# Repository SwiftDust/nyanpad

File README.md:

# Nyanpad

My macropad, built for [Hackpad](https://hackpad.hackclub.com)! It features LED backlighting, an OLED screen and 4 keys to control your music :)

## CAD
https://cad.onshape.com/documents/298fb66352279c3f6c87f3de/w/c801169e636e5dfcfdb9d4bb/e/7bab212490aaadabd4187f28?renderMode=0&uiState=6afa35f24b47de4cd4f44e78

## Schematic

## PCB

## BOM

| Qty | Item | Price (USD) | Link |
|---|---|---|---|
| 4x | Cherry MX Switches | 5,29 | https://nl.aliexpress.com/item/1005012832907656.html?spm=a2g0o.productlist.main.16.54f74710lBx9J8&algo_pvid=466906ea-7de0-4691-b869-b8c9dada8754&algo_exp_id=466906ea-7de0-4691-b869-b8c9dada8754-15&pdp_ext_f={%22order%22%3A%2254%22%2C%22eval%22%3A%221%22%2C%22fromPage%22%3A%22search%22}&pdp_npi=6%40dis!EUR!5.37!4.79!!!5.80!5.18!%400b88a95617947775685107257e0f20!12000059458181010!sea!NL!0!X!1!0!n_tag%3A-29919%3Bd%3Aeac98f9%3Bm03_new_user%3A-29895%3BpisId%3A5000000220770329&curPageLogUid=bMwGbcEopLZR&utparam-url=scene%3Asearch|query_from%3A|x_object_id%3A1005012832907656|_p_origin_prod%3A |
| 4x | DSA keycaps | 1,59 | https://nl.aliexpress.com/item/1005013428750906.html?spm=a2g0o.productlist.main.13.7f60bf6anoDfJp&algo_pvid=8e305201-02fd-4fef-ae02-85556622e4f5&algo_exp_id=8e305201-02fd-4fef-ae02-85556622e4f5-12&pdp_ext_f={%22order%22%3A%2210%22%2C%22eval%22%3A%221%22%2C%22fromPage%22%3A%22search%22}&pdp_npi=6%40dis!EUR!0.35!0.36!!!2.49!2.58!%400b15832917947779250776391e0fc9!12000061069461267!sea!NL!0!X!1!0!n_tag%3A-29919%3Bd%3Aeac98f9%3Bm03_new_user%3A-29895&curPageLogUid=Cd40D66sFnz9&utparam-url=scene%3Asearch|query_from%3A|x_object_id%3A1005013428750906|_p_origin_prod%3A |
| 5x | M3x5x4 heatset inserts | 4,51 | https://nl.aliexpress.com/item/1005010155305523.html?spm=a2g0o.productlist.main.1.5f0a3c4fNBxcuN&algo_pvid=e5bb6dcb-2cde-4527-a1a4-0230e28a1f05&algo_exp_id=e5bb6dcb-2cde-4527-a1a4-0230e28a1f05-0&pdp_ext_f={%22order%22%3A%2210565%22%2C%22eval%22%3A%221%22%2C%22orig_sl_item_id%22%3A%221005010155305523%22%2C%22orig_item_id%22%3A%221005013150425438%22%2C%22fromPage%22%3A%22search%22}&pdp_npi=6%40dis!EUR!8.18!4.09!!!58.89!29.44!%400b88ab8a17947781676843401e0e3c!12000051347301636!sea!NL!0!X!1!0!n_tag%3A-29919%3Bd%3Aeac98f9%3Bm03_new_user%3A-29895&curPageLogUid=PFmU9B7g3e2J&utparam-url=scene%3Asearch|query_from%3A|x_object_id%3A1005010155305523|_p_origin_prod%3A1005013150425438 |
| 6x | 1N4148 DO-35 diodes | 0,47 | https://www.lcsc.com/product-detail/C402212.html?s_z=n_q_t_1N4148 |
| 4x | SK6812 MINI-E LEDs  | 0,41 | https://www.lcsc.com/product-detail/C5149201.html?s_z=s_q_SK6812MINI-E |
| 1x | 0,91" 128x32 OLED display | 2,27 | https://www.lcsc.com/product-detail/C5248081.html?s_z=s_c_LCD%252C%2520OLED%252C%2520Graphic |
| 1x | XIAO RP2040 | 3,90 | https://www.seeedstudio.com/XIAO-RP2040-v1-0-p-5026.html |
| 1x | PCB | 4,00 | https://jlcpcb.com/ |
| | Total | 22,44 | |
| | Total with shipping* | 49,73

*Shipping: 2,79 for shipping JLCPCB to LCSC, 13,90 to ship that order to me, 8,16 for the SEED XIAO RP2040 and 2,44 for the Aliexpress order. Printing Legion not yet included.

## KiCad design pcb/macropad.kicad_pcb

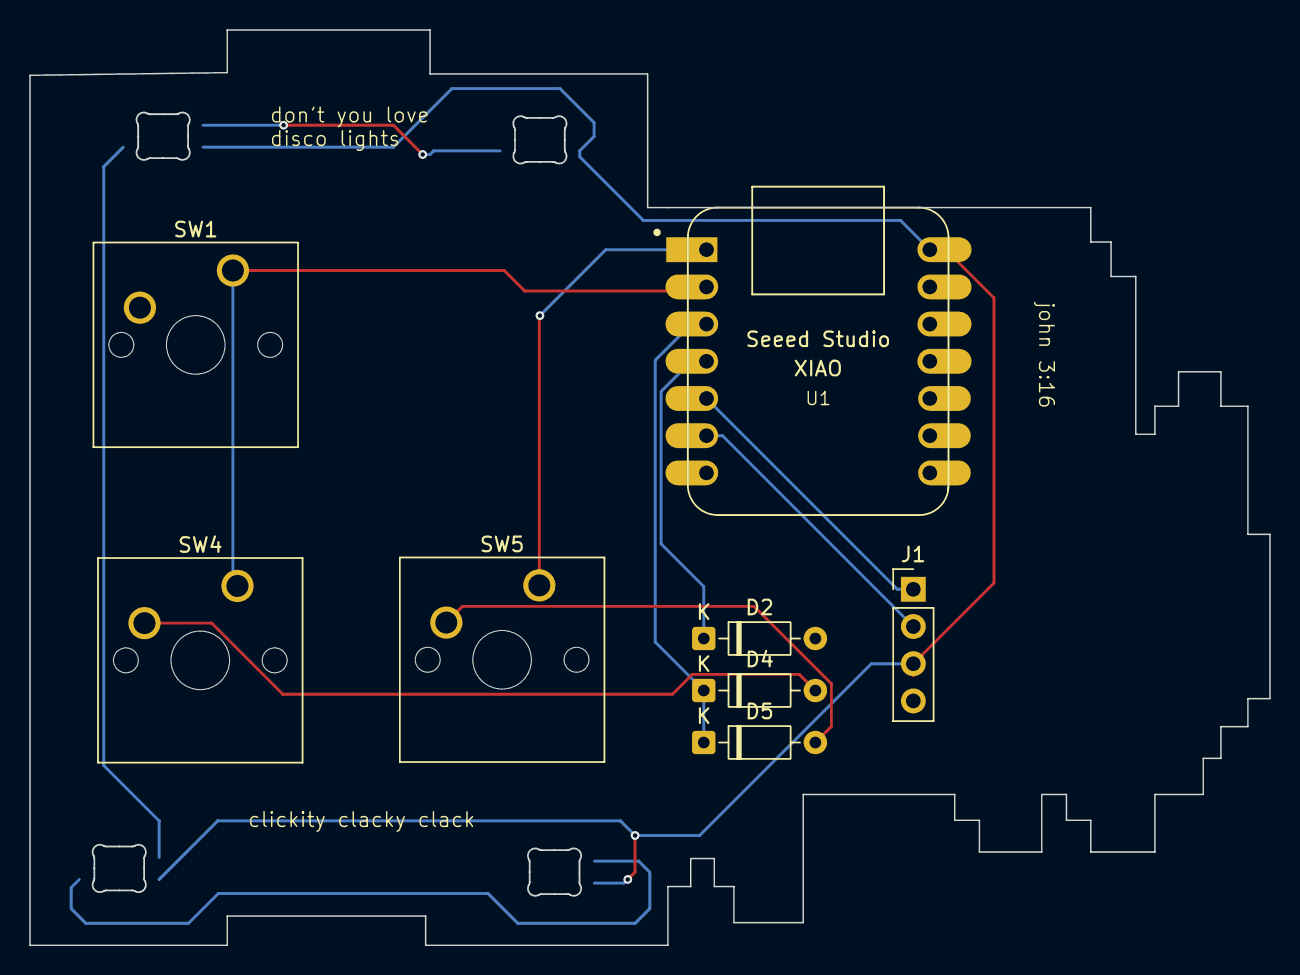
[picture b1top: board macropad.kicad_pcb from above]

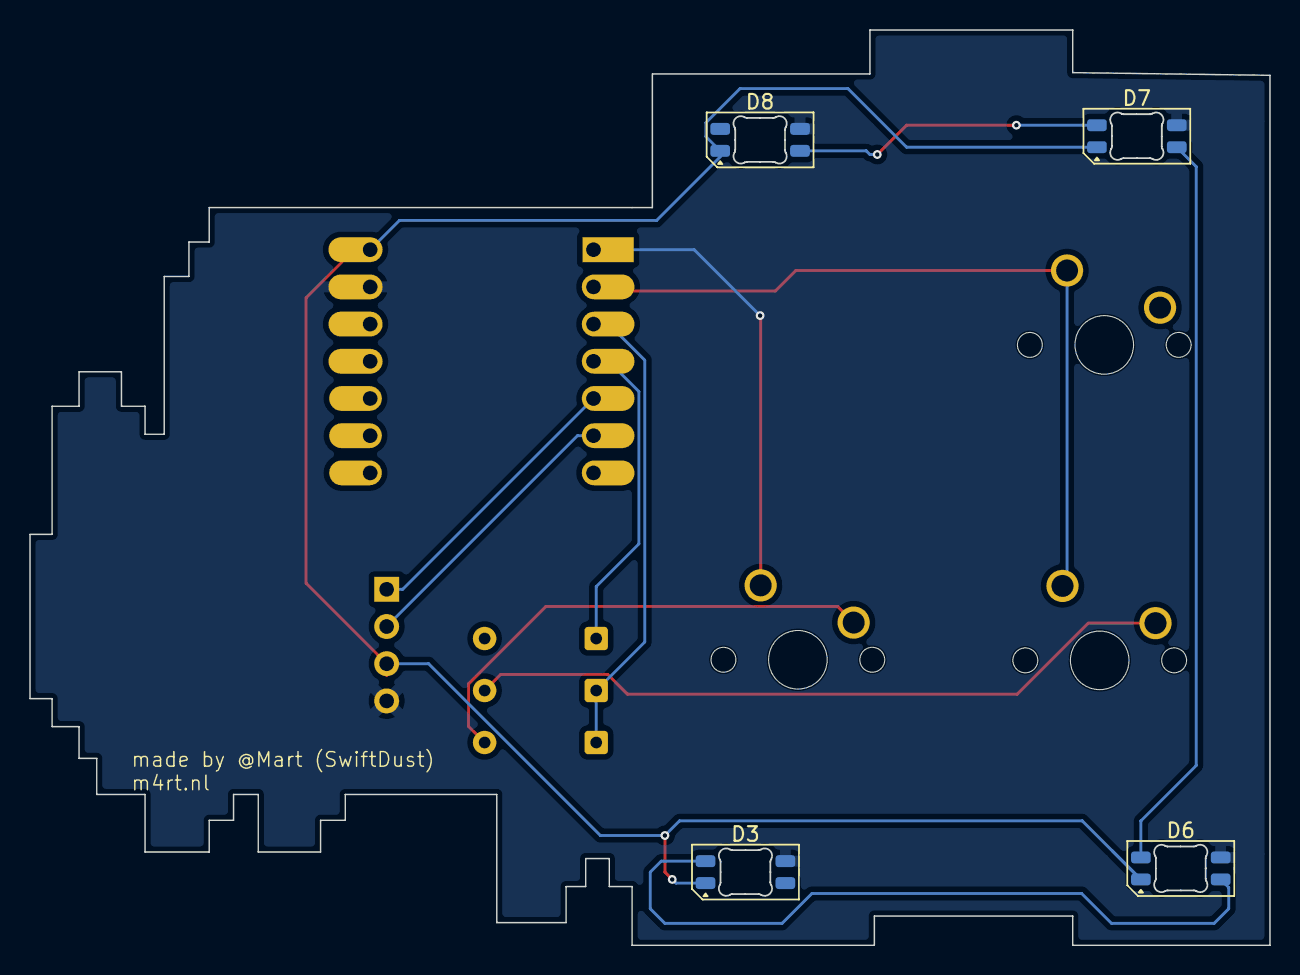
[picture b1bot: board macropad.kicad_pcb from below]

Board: 2 copper layers, 84.7 x 62.5 mm, 12 parts (4 on the bottom side), 13 nets.

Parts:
D2, D4, D5: D; D_DO-35_SOD27_P7.62mm_Horizontal
D3, D6, D7, D8: SK6812MINI-E; LED_SK6812MINI-E_3.2x2.8mm_P1.5mm_ReverseMount
J1: OLED_DISPLAY; PinHeader_1x04_P2.54mm_Vertical
SW1, SW4, SW5: SW_Push_45deg; SW_Cherry_MX_1.00u_PCB
U1: MOUDLE-SEEEDUINO-XIAO; XIAO-Generic-Hybrid-14P-2.54-21X17.8MM

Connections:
/COL0: SW1.1, SW4.1, U1.2 (PA4_A1_D1)
/COL1: SW5.1, U1.1 (PA02_A0_D0)
/ROW0: D2.1 (K), U1.4 (PA11_A3_D3)
/ROW1: D4.1 (K), D5.1 (K), U1.3 (PA10_A2_D2)
/SCL: J1.2, U1.6 (PA9_A5_D5_SCL)
/SDA: J1.1, U1.5 (PA8_A4_D4_SDA)
GND: D3.3 (VSS), D6.3 (VSS), D7.3 (VSS), D8.3 (VSS), J1.4, U1.13 (GND)
unnamed: D3.2 (DOUT), D6.4 (DIN)
unnamed: D4.2 (A), SW4.2
unnamed: D5.2 (A), SW5.2
unnamed: D6.2 (DOUT), D7.4 (DIN)
unnamed: D7.2 (DOUT), D8.4 (DIN)
VCC: D3.1 (VDD), D6.1 (VDD), D7.1 (VDD), D8.1 (VDD), J1.3, U1.14 (5V)
